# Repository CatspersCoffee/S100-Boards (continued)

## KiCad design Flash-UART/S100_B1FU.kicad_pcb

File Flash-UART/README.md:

# RS232 | TMA | Serial Flash Board Rev 1.0

An S-100 board with a USB serial port (16550 + FT232R), four TMA* bus-master request lines, and four SPI flash chips. The flash chips can be loaded from a PC over USB and then read from the S-100 side (2014–2015).

The idea is fast development turnaround:
1. Program the SPI flash chips from a PC through the CH341A.
2. Flip the RUN/FLASH switch.
3. An S-100 monitor/loader reads the flash contents into RAM through the CPLD's I/O ports.

The S-100 monitor/loader and the PIC18F1330 firmware are **not** in this repo.

## Status
Built. The gerbers are dated 16 Apr 2014 (`GERBERS/`). The CPLD design was brought up in June 2014 and revised in July and December 2015.

## Hardware
| Ref | Part | Role |
|---|---|---|
| U20 | XC95288XL-TQ144 | CPLD: S-100 glue, port decode, SPI bit-bang registers, flash chip select |
| Ux18 | 16550 | UART (clock from oscillator socket Px12 "CLK UART") |
| Ux21 | FT232R | USB to serial for the UART (Jx1) |
| U18 | CH341A | USB to SPI flash programmer (Jx2, 12 MHz crystal X1) |
| U14–U17 | M25P80 | SPI flash chips on a shared bus (U14 on top, U15–U17 on the bottom) |
| U12 | 74LV244 | Switches the flash bus between the CPLD and the CH341A |
| U8 | PIC18F1330 | Reads the RUN/FLASH and F_SEL switches and drives the U12 enables |
| Ux17 | 74LS682N | UART I/O address compare against DIP switch SWx2 |
| U3din1, U3dout1 | 74LS541 | S-100 DO → local data bus, local data bus → S-100 DI |
| U4, U5, U6 | 74LS541 | Address buffers A0–A23 |
| U11 | 74LS541 | TMA0*–TMA3* drivers |
| U19 | 74LS541 | Puts the flash data-out bit on local D0 |
| U7a1, U7b1 | 74HC245 | S-100 status/control input buffers |
| U2, U1, Ux1 | LM1086CS, 7805, 3.3 V SOT-223 | Power |

- **Board:** 10.0 × 5.0 in (254 × 127 mm), plus the S-100 edge-connector tab.
- **KiCad:** pcbnew `(2013-07-07 BZR 4022)-stable`, legacy schematic format (`EESchema Schematic File Version 2`).
- **CPLD tools:** Xilinx ISE 14.7 (`P.20131013`), XC95288XL-10-TQ144.
- **Switches:** RESET (SW1), PIC RESET (SW2), F_SEL (SW4), RUN/FLASH (SW50), DIP switch SWx2 (UART address: A3–A7 on sw 1–5, IORQ on sw 6, sw 7 and 8 to GND).
- **LEDs:** TMA0–TMA3, DONE, B_S (board select), D2, D3, F0–F3 (flash selected), RUN, PROG, TX, RX, and power LEDs for the board, the FT232R and the CH341A.
- **Headers:**
  - XILINX CABLE (JTAG), PIC ISP, FLASH ICP (GND, CLK, Din, CS, Dout on the CH341A side), UART INT
  - CPLD I/O (P10: P110–P112, P2: P113/P115/P116)
  - RDY (P72), RESET (P75)
  - Interrupt Channel Selector (VI0*–VI7*)

## How it works
- **I/O request:** the CPLD makes IOREQ from sINP OR sOUT and passes it to the 74LS682. When A7–A3 and IOREQ match SWx2, the 74LS682 selects the 16550. A2–A0 go straight to the UART. The CPLD makes the UART's RD*/WR* strobes from pDBIN/pWR* and drives the two data-bus buffers.
- **SPI flash ports:** the CPLD decodes ports 90h–97h. A3 is not decoded, so 98h–9Fh mirror them. Each write latches D0, except port 96h, which takes D0–D2.

  | Port | Function |
  |---|---|
  | 90h | CLK |
  | 91h | Din (data to flash) |
  | 92h | CS |
  | 93h | read flash data-out on D0 |
  | 94h | DONE LED |
  | 95h | bit 0: flash select source |
  | 96h | bits 2..0: flash number |

  A loader bit-bangs SPI through these ports.
- **Flash chip select:** the CS from whichever side owns the bus (CPU or CH341A) goes through a 3-to-8 decoder in the CPLD to FLASHSEL0–3 (U14–U17). LEDs F0–F3 show which chip is selected.
  - After reset (port 95h bit 0 = 0) the selection is U16. A note in the CPLD schematic says this position was used for a 256 KB 25L020 "for quick programming".
  - With bit 0 = 1, port 96h picks the chip.
  - In the 2014 CPLD versions the PIC chose the chip instead, through lines PIC18F_0..2.
- **CH341A or S-100:** all four flash chips share CLK/Din/Dout. One half of the 74LV244 connects them to the CPLD, the other half to the CH341A and the FLASH ICP header. The PIC18F1330 enables one half or the other, following the RUN/FLASH switch. At power-up the CPLD (S-100) side has the bus.
- **TMA:** an OUT to port **EEh** latches D0–D3 onto TMA0*–TMA3* (S-100 pins 55, 56, 57, 14) through U11. In U20v2 a 1 asserts the line (low), and reset leaves all four lines high.
- **Reset:** S-100 SLAVE_CLR*, the RESET button or a PIC line clears the CPLD registers and resets the UART. The RESET button also pulls S-100 RESET* (pin 75) through Q8 and jumper JP4.
- **UART:** the 16550's TTL serial lines (SIN, SOUT, RTS, CTS, DTR, DSR) go to the FT232R and USB socket Jx1. The UART interrupt goes to the "UART INT" jumper.

## Files
| Path | What |
|---|---|
| `S100_B1FU.sch`, `S100_B1FU-cache.lib`, `S100_B1FU.pro` | KiCad schematic, symbol cache, project |
| `S100_B1FU.kicad_pcb` | KiCad PCB |
| `S100_B1FU.net`, `S100_B1FU.cmp` | Netlist and component/footprint list |
| `GERBERS/` | Fabrication gerbers and drill file (16 Apr 2014) |
| `cpld/U20v2.sch` | Current CPLD schematic (Xilinx ISE schematic, XML) |
| `cpld/U20v1.sch` | Previous CPLD schematic (July 2015) |
| `cpld/pinmap.ucf` | CPLD pin constraints |
| `cpld/S100BFURev1/S100BFURev1.xise` | ISE project (top: `../U20v2.sch`, constraints `../pinmap.ucf`) |
| `cpld/S100BFURev1/U20v1.jed`, `U20v2.jed` | Programming files |
| `cpld/outdated/` | The first U20 test schematic and pin map (May 2014) |

## History
The git history replays the original dated backups of the KiCad project and the CPLD project, from April 2014 to December 2015.

## Things to check (TODO)
- On the PCB, 16550 (Ux18) pins 18 (WR*), 21 (RD*) and 35 (MR) have no net. The CPLD's RD, WR and RESET outputs (pins 113, 116, 115) only go to header P2. Check the wiring from P2 to the UART.
- CPLD pin 39 (`IOREQtoUx17`, an output) and U7a1 pin 6 (74HC245 output from S-100 pin 69) are on the same net (`/IOREQbb`). Check that only one of them drives it.

## Credits
- The UART section (16550 and FT232R with TTL serial labels, and its schematic notes) follows the N8VEM ECB SBC V2 schematic. Credit to Andrew Lynch and the N8VEM project.
- KiCad symbol libraries include N8VEM community libraries.

## License
Hardware: CERN-OHL-S-2.0 for the original work in this folder; see the repo NOTICE for third-party parts. The bottom-copper text "© 2014 Antony Burrows ALL RIGHTS RESERVED" is left as fabricated; this license applies.

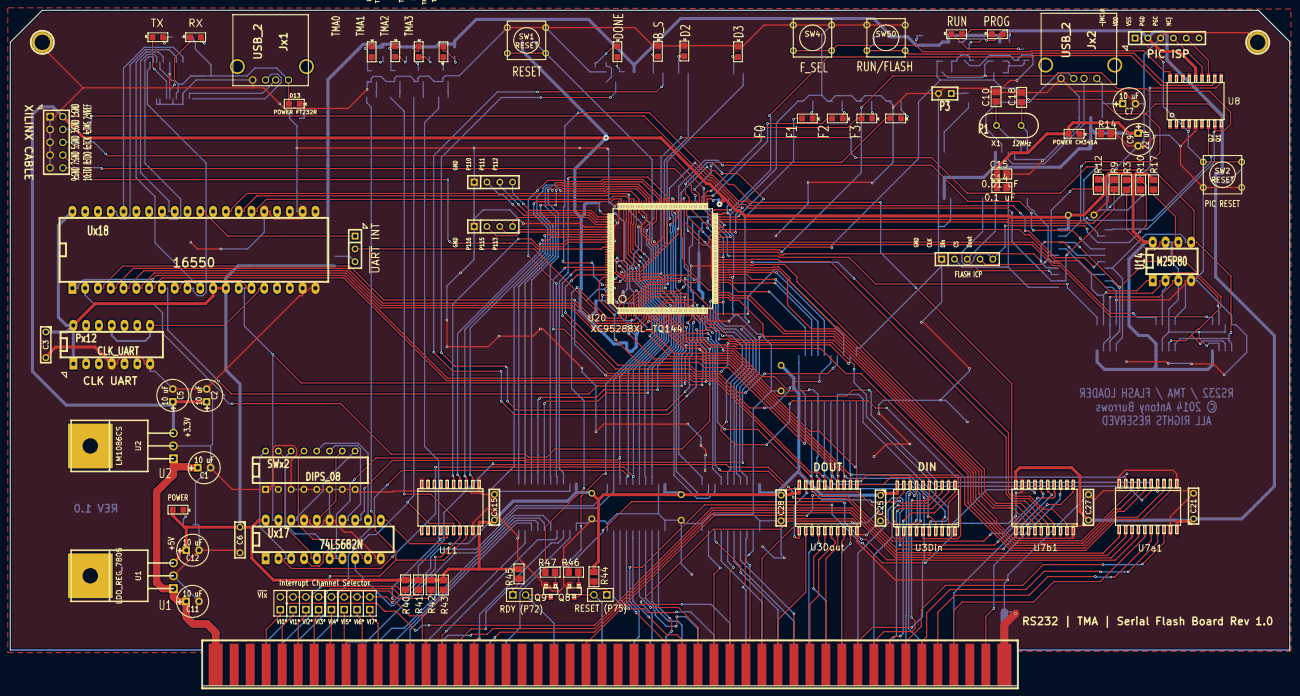
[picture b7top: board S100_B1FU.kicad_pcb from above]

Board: 2 copper layers, 254.0 x 134.1 mm, 164 parts (0 on the bottom side), 254 nets.

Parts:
C1, C2, C5, C7, C11, C12: 10 uF; C1V7
C3, C4, C6, C8, C17, C20, C21, C25, C27, C28: 0.1 uF; C2
C9: 22 uF; C1V7
C10, C18: 15 pF; ^^SMD_Resistor-0805
C14: 0.1 uF; ^^SMD_Resistor-0805
C15: 0.01 uF; ^^SMD_Resistor-0805
C19, C26, C33, C34, C35, C36, C37, C38, C39, C40: C; ^^SMD_Resistor-0805
Cx15: 0.1 uF; C2
D1, D4: LED; ^^LED-0805
D2: P55; ^^LED-0805
D3: P54; ^^LED-0805
D5: POWER; ^^LED-0805
D6: DONE; ^^LED-0805
D7: BOARD_SELECT; ^^LED-0805
D8: POWER CH341A; ^^LED-0805
D9: FLASH_0; ^^LED-0805
D10: FLASH_1; ^^LED-0805
D11: FLASH_2; ^^LED-0805
D12: FLASH_3; ^^LED-0805
D13: POWER FT232R; ^^LED-0805
D14: TMA0; ^^LED-0805
D15: TMA1; ^^LED-0805
D16: TMA2; ^^LED-0805
D17: TMA3; ^^LED-0805
Dx2, Dx3: LED; ^^LED-0805
JP4, JP5: JUMPER; PIN_ARRAY_2X1
JPx1, JPx2, JPx3, JPx4, JPx5, JPx6, JPx7, JPx8: JUMPER; PIN_ARRAY_2X1
Jx1, Jx2: USB_2; USB_A
Kx1: CONN_3; SIL-3
P1: M25P80 ISP; SIL-5
P2, P10: CONN_4; SIL-4
P3: CONN_2; SIL-2
P4: S100_MALE
P5: PIC_ISP; SIL-6
P6, P7: CONN_1; 1pin
P8, P9: CONN_2; ^^SMD_Resistor-0805
P19: XILINX CABLE2; PIN_ARRAY_5x2
Px12: CLK_UART; DIP-14__300_ELL
Q1, Q2, Q3, Q4, Q5, Q6, Q7, Q8, Q9: ^^NPN-SOT23; ^^-SOT23
R1, R5, R6, R13, R14, R15, R16, R20, R21, R22, R23, R24, R29, R31, R33, R35, R37, R39, R40, R41, R42, R43, R44, R45: 330; ^^SMD_Resistor-0805
R2, R7, R18, R19, R28, R32, R34, R36, R38, R46, R47: 470; ^^SMD_Resistor-0805
R3: 1K; ^^SMD_Resistor-0805
R4, R8, R10, R11, R30: 10k; ^^SMD_Resistor-0805
R9, R12, R17: 10K; ^^SMD_Resistor-0805
R25, R26, R27: 100; ^^SMD_Resistor-0805
Rx2: 4700; ^^SMD_Resistor-0805
Rx7, Rx8: 330; ^^SMD_Resistor-0805
SW1, SW2: RESET; SW_PUSH_SMALL
SW4: FLASH_SELECT; SW_PUSH_SMALL
SW50: FLASH/RUN; SW_PUSH_SMALL
SWx2: DIPS_08; 16dip300
U1: LDO_REG_7805; ^^TO220
U2: LM1086CS; ^^TO220
U3din1, U3dout1, U4, U5, U6, U11, U19: ^^74LS541; ^^-SO20W
U7a1, U7b1: 74HC245; ^^-SO20W
U8: PIC18F1330; -SO18-1
U12: ^^74LV244; ^^-SO20W
U14: M25P80; 8DIP-ELL300
U15, U16, U17: M25P80; -SO8
U18: CH341A; -SO28W
U20: XC95288XL-TQ144; -TQFP144
Ux1: ^^3.3VREG_SOT223; -SOT223
Ux17: 74LS682N; 20DIP-ELL300
Ux18: 16550; DIP-40__600_ELL
Ux21: FT232R; -SSOP28
X1: 12MHz; Crystal_HC-49U_Vert

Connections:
/+8V: C1.1, C11.1, P4.1, P4.51, U1.1, U2.1
//CS_UART: U20.25, Ux17.19, Ux18.14
//M1: U7a1.2, U20.20
//WAITtoS100: R47.1, U20.2
/A0: U4.18, U20.100, Ux18.28
/A0b: P4.79, U4.2
/A1: U4.17, U20.101, Ux18.27
/A1b: P4.80, U4.3
/A2: U4.16, U20.102, Ux18.26
/A2b: P4.81, U4.4
/A3: U4.15, U20.103, Ux17.2
/A3b: P4.31, U4.5
/A4: U4.14, U20.104, Ux17.4
/A4b: P4.30, U4.6
/A5: U4.13, U20.105, Ux17.6
/A5b: P4.29, U4.7
/A6: U4.12, U20.106, Ux17.8
/A6b: P4.82, U4.8
/A7: U4.11, U20.107, Ux17.11
/A7b: P4.83, U4.9
/A8: U5.18, U20.79
/A8b: P4.84, U5.2
/A9: U5.17, U20.80
/A9b: P4.34, U5.3
/A10: U5.16, U20.81
/A10b: P4.37, U5.4
/A11: U5.15, U20.82
/A11b: P4.87, U5.5
/A12: U5.14, U20.83
/A12b: P4.33, U5.6
/A13: U5.13, U20.85
/A13b: P4.85, U5.7
/A14: U5.12, U20.86
/A14b: P4.86, U5.8
/A15: U5.11, U20.87
/A15b: P4.32, U5.9
/A16: U6.18, U20.88
/A16b: P4.16, U6.2
/A17: U6.17, U20.91
/A17b: P4.17, U6.3
/A18: U6.16, U20.92
/A18b: P4.15, U6.4
/A19: U6.15, U20.93
/A19b: P4.59, U6.5
/A20: U6.14, U20.94
/A20b: P4.61, U6.6
/A21: U6.13, U20.95
/A21b: P4.62, U6.7
/A22: U6.12, U20.96
/A22b: P4.63, U6.8
/A23: U6.11, U20.97
/A23b: P4.64, U6.9
/BOARD_INTERRUPT_VECT: U7b1.9, U20.5
/BOARD_INTERRUPT_VECTc: JPx1.2, JPx2.2, JPx3.2, JPx4.2, JPx5.2, JPx6.2, JPx7.2, JPx8.2, U7b1.11
/BOARD_SEL_LED: R20.2, U20.31
/CLK_UART: Px12.8, Px12.11, Ux18.16
/CLOCK*: P4.49, U7b1.13
/CLOCK*b: U7b1.7, U20.53
/CPLD2_TCK: R25.1, U20.67
/CPLD2_TDI: R26.1, U20.63
/CPLD2_TDO: P19.8, U20.122
/CPLD2_TMS: R27.1, U20.65
/CPLD_45: U19.2, U20.45
/CPLD_46: U19.3, U20.46
/CPLD_48: U19.4, U20.48
/CPLD_49: U19.5, U20.49
/CPLD_130: U19.6, U20.130
/CPLD_131: U19.7, U20.131
/CPLD_132: U19.8, U20.132
/CPLD_133: U19.9, U20.133
/CPLD_134: U19.1, U19.19, U20.134
/CPLD_M25P80_CLK: U12.2, U20.135
/CPLD_M25P80_CS: U12.6, U20.137
/CPLD_M25P80_Din: U12.4, U20.136
/CPLD_M25P80_Dout: R9.2, U12.12, U20.138
/CTS_TTL: Ux18.36, Ux21.11
/D0: U3din1.18, U3dout1.2, U19.18, U20.9, U20.17, Ux18.1
/D1: U3din1.17, U3dout1.3, U19.17, U20.10, U20.19, Ux18.2
/D2: U3din1.16, U3dout1.4, U19.16, U20.11, Ux18.3
/D3: U3din1.15, U3dout1.5, U19.15, U20.12, Ux18.4
/D4: U3din1.14, U3dout1.6, U19.14, U20.13, Ux18.5
/D5: U3din1.13, U3dout1.7, U19.13, U20.14, Ux18.6
/D6: U3din1.12, U3dout1.8, U19.12, U20.15, Ux18.7
/D7: U3din1.11, U3dout1.9, U19.11, U20.16, Ux18.8
/DBUSIN_EN: U3din1.1, U3din1.19, U20.22
/DBUSOUT_EN: U3dout1.1, U3dout1.19, U20.21
/DI0b: P4.95, U3dout1.18
/DI1b: P4.94, U3dout1.17
/DI2b: P4.41, U3dout1.16
/DI3b: P4.42, U3dout1.15
/DI4b: P4.91, U3dout1.14
/DI5b: P4.92, U3dout1.13
/DI6b: P4.93, U3dout1.12
/DI7b: P4.43, U3dout1.11
/DO0b: P4.36, U3din1.2
/DO1b: P4.35, U3din1.3
/DO2b: P4.88, U3din1.4
/DO3b: P4.89, U3din1.5
/DO4b: P4.38, U3din1.6
/DO5b: P4.39, U3din1.7
/DO6b: P4.40, U3din1.8
/DO7b: P4.90, U3din1.9
/DONE_LED: R7.2, U20.30
/DSR_TTL: Ux18.37, Ux21.9
/DTR_TTL: Ux18.33, Ux21.2
/FLASH_0: D9.1, U20.71
/FLASH_1: D10.1, U20.74
/FLASH_2: D11.1, U20.75
/FLASH_3: D12.1, U20.76
/FLASH_CS: U12.5, U12.14, U20.57
/FLASH_SEL_0: U14.1, U20.66
/FLASH_SEL_1: U15.1, U20.64
/FLASH_SEL_2: U16.1, U20.61
/FLASH_SEL_3: U17.1, U20.60
/IOREQb: P4.69, U7a1.14
/IOREQbb: U7a1.6, U20.39, Ux17.13
/LED_D2: R13.2, U20.7
/LED_D3: R16.2, U20.6
/M2_MCLR: P5.1, R4.2, SW2.1, U8.4
/M2_PGC: P5.5, U8.12
/M2_PGD: P5.4, U8.13
/MWRT: P4.68, U7a1.13
/MWRTb: U7a1.7, U20.40
/NDEF2: P4.65, U7a1.12
/NDEF2b: U7a1.8, U20.41
/PHI: P4.24, U7b1.14
/PHIb: U7b1.6, U20.54
/PIC18F_0: U8.11, U20.68
/PIC18F_1: U8.10, U20.69
/PIC18F_2: U8.7, U20.70
/PROG_M25P80_CLK: P1.2, U12.11, U18.18
/PROG_M25P80_CS: P1.4, U12.15, U18.15
/PROG_M25P80_Din: P1.3, U12.13, U18.20
/PROG_M25P80_Dout: P1.5, R10.2, U12.3, U18.22
/Q1: R2.2, R18.2, U8.9, U12.19, U20.59
/Q2: R19.2, R28.2, U8.8, U12.1, U20.58
/RDY: JP5.2, P4.72, Q9.3
/RESET*: JP4.2, P4.75, Q8.3
/RESETtoS100: R46.1, U20.3
/RTS_TTL: Ux18.32, Ux21.3
/SIN_TTL: Ux18.10, Ux21.1
/SLAVE_CLR*: P4.54, U7a1.11
/SLAVE_CLR*vv: U7a1.9, U20.33
/SOUT_TTL: Ux18.11, Ux21.5
/TMA0*: P4.55, R32.1, R40.1, U11.18
/TMA0_CPLD: U11.2, U20.117
/TMA1*: P4.56, R34.1, R41.1, U11.17
/TMA1_CPLD: U11.3, U20.118
/TMA2*: P4.57, R36.1, R42.1, U11.16
/TMA2_CPLD: U11.4, U20.119
/TMA3*: P4.14, R38.1, R43.1, U11.15
/TMA3_CPLD: U11.5, U20.120
/UART_INT: Kx1.1, Ux18.30
/USB_VCC0: D13.1, Jx1.1, Rx7.1, Rx8.1, Ux21.4, Ux21.20
/USB_VCC1: C7.1, Jx2.1, Ux1.3
/V3.3: C2.1, C4.1, C5.1, C19.1, C26.1, C33.1, C34.1, C35.1, C36.1, C37.1, C38.1, C39.1, C40.1, P8.1, P8.2, P9.1, P9.2, P19.2, R3.2, R8.1, R12.1, R17.1, U2.3, U12.20, U14.8, U15.8, U16.8, U17.8, U20.1, U20.8, U20.37, U20.42, U20.55, U20.73, U20.84, U20.109, U20.127, U20.141
/V3.3b: C9.1, C14.1, C15.1, D8.1, U18.9, U18.28, Ux1.2, Ux1.4
/VI0*: JPx1.1, P4.4
/VI1*: JPx2.1, P4.5
/VI2*: JPx3.1, P4.6
/VI3*: JPx4.1, P4.7
/VI4*: JPx5.1, P4.8
/VI5*: JPx6.1, P4.9
/VI6*: JPx7.1, P4.10
/VI7*: JPx8.1, P4.11
/pDBIN: P4.78, U7b1.16
/pDBINb: U7b1.4, U20.51
/pWR*: P4.77, U7b1.17
/pWR*b: U7b1.3, U20.50
/sINP: P4.46, U7a1.16
/sINPb: U7a1.4, U20.35
/sM1: P4.44, U7a1.18
/sMEMR: P4.47, U7a1.15
/sMEMRb: U7a1.5, U20.38
/sOUT: P4.45, U7a1.17
/sOUTb: U7a1.3, U20.34
/sWO*: P4.97, U7b1.15
/sWO*b: U7b1.5, U20.52
/~UART_INT: Kx1.2, U20.4
GND: C1.2, C2.2, C3.2, C4.2, C5.2, C6.2, C7.2, C8.2, C9.2, C10.2, C11.2, C12.2, C14.2, C15.2, C17.2, C18.2, C19.2, C20.2, C21.2, C25.2, C26.2, C27.2, C28.2, C33.2, C34.2, C35.2, C36.2, C37.2, C38.2, C39.2, C40.2, Cx15.2, D2.2, D3.2, D7.2, Jx1.4, Jx2.4, P1.1, P2.1, P3.2, P4.50, P4.100, P5.3, P6.1, P7.1, P10.1, P19.1, P19.3, P19.5, P19.7, P19.9, Px12.4, Px12.7, Q1.2, Q2.2, Q3.2, Q4.2, Q5.2, Q6.2, Q7.2, Q8.2, Q9.2, R5.2, R9.1, R10.1, R14.2, R21.1, R22.1, R23.1, R24.1, R31.2, SW1.1, SW2.2, SW4.1, SW50.1, SWx2.1, SWx2.2, SWx2.3, SWx2.4, SWx2.5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
unnamed: R15.2, U18.1
unnamed: P10.4, U20.110
unnamed: P10.3, U20.111
unnamed: P10.2, U20.112
unnamed: P2.4, U20.113
unnamed: P2.3, U20.115
unnamed: P2.2, U20.116
unnamed: D17.1, R39.1
unnamed: Q7.1, R38.2
unnamed: D16.2, Q6.3
unnamed: D16.1, R37.1
unnamed: Q6.1, R36.2
unnamed: D17.2, Q7.3
unnamed: JP5.1, R45.1
unnamed: Q9.1, R47.2
unnamed: JP4.1, R44.1
unnamed: Q8.1, R46.2
unnamed: D14.1, R33.1
unnamed: D14.2, Q4.3
unnamed: Q4.1, R32.2
unnamed: D15.1, R35.1
unnamed: D15.2, Q5.3
unnamed: Q5.1, R34.2
unnamed: R8.2, SW1.2, U20.24
unnamed: P3.1, R15.1
unnamed: D8.2, R14.1
unnamed: Jx2.2, U18.11
unnamed: Jx2.3, U18.10
unnamed: C10.1, U18.13, X1.1
unnamed: C18.1, U18.14, X1.2
unnamed: D9.2, R21.2
unnamed: D10.2, R22.2
unnamed: D11.2, R23.2
unnamed: D12.2, R24.2
unnamed: R11.2, SW4.2, U8.18
unnamed: D4.2, Q2.3
unnamed: D13.2, R31.1
unnamed: Ux18.9, Ux18.15
unnamed: Dx2.2, Ux21.23
unnamed: Dx3.2, Ux21.22
unnamed: Dx2.1, Rx7.2
unnamed: Dx3.1, Rx8.2
unnamed: Jx1.2, Ux21.16
unnamed: Jx1.3, Ux21.15
unnamed: Kx1.3, Rx2.2
unnamed: P19.10, R26.2
unnamed: P19.6, R25.2
unnamed: P19.4, R27.2
unnamed: R30.2, SW50.2, U8.17
unnamed: D4.1, R29.1
unnamed: SWx2.16, Ux17.3
unnamed: SWx2.15, Ux17.5
unnamed: SWx2.14, Ux17.7
unnamed: SWx2.13, Ux17.9
unnamed: SWx2.11, Ux17.14
unnamed: SWx2.12, Ux17.12
unnamed: SWx2.10, Ux17.16
unnamed: SWx2.9, Ux17.18
unnamed: D1.1, R1.1
unnamed: D1.2, Q1.3
unnamed: R3.1, U14.3, U14.7, U15.3, U15.7, U16.3, U16.7, U17.3, U17.7
unnamed: R12.2, U12.7, U12.16, U14.5, U15.5, U16.5, U17.5
unnamed: R17.2, U12.9, U12.18, U14.6, U15.6, U16.6, U17.6
unnamed: U12.8, U12.17, U14.2, U15.2, U16.2, U17.2
unnamed: D6.1, R6.1
unnamed: D6.2, Q3.3
unnamed: Q3.1, R7.1
unnamed: D5.2, R5.1
unnamed: D7.1, R20.1
unnamed: D2.1, R13.1
unnamed: Q2.1, R18.1, R28.1
unnamed: Q1.1, R2.1, R19.1
unnamed: D3.1, R16.1
VCC: C3.1, C6.1, C8.1, C12.1, C17.1, C20.1, C21.1, C25.1, C27.1, C28.1, Cx15.1, D5.1, P5.2, Px12.1, Px12.14, R1.2, R4.1, R6.2, R11.1, R29.2, R30.1, R33.2, R35.2, R37.2, R39.2, R40.2, R41.2, R42.2, R43.2, R44.2, R45.2, Rx2.1, U1.3, U3din1.20, U3dout1.20, U4.20, U5.20, U6.20, U7a1.20, U7b1.20, U8.14, U11.20, U19.20, Ux17.20, Ux18.12, Ux18.13, Ux18.40

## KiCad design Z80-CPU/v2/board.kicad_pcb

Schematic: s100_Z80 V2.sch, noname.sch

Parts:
C1: 47 uF; C1V7
C2, C4: 0.1 uF
C3: 0.1 uF; C1V7
C7, C8, C9, C10, C11, C12, C13, C14, C15, C16, C18, C19, C20, C23, C24, C25, C26, C27, C28, C29, C30, C36, C37, C38, C39, C40, C41, C45, C46, C47, C48, C49, C50, C51, C52, C53, C54, C58, C59, C60, C62, C63: 0.1 uF; C2
C42: 22 uF; C1V7
C43: 33 uF; C1V7
D1, D2, D3, D4, D5, D7: DONE
D6: 1N4148; D3
JP4, JP5, JP6, JP7: JUMPER; SIL-2
K1, K2, K4: CONN_3; SIL-3
P1: S100_MALE
P2: CONN_4X2; pin_array_4x2
P3, P5: CLK_CPU
P4, P37: CONN_2X2; PIN_ARRAY_2X2
P6: CLK_SEL
P34, P35: CONN_1; 1pin
P36: CONN_3X2; pin_array_3x2
Px1, Px2, Px3, Px4, Px5: CONN_8
Q1: 2N3904; TO92-INVERT
Q2, Q3, Q4, Q5, Q6, Q7: ^^NPN-SOT23
R1, R3, R7, R9, R12, R14: 330
R2, R6, R8, R10, R13, R15: 470
R4: 4K7; R3
R5: 330; R3
R11, R39, R41: 4700; R3
R35, R36, R37, R38: 10; R3
RR2, RR3, RR4, RR5, RR6, RR8, RR9: 1000; r_pack9
RR7: 4700; r_pack9
SW2, SW3, SW4: DIPS_08; SWDIP8
U, U43: 74LS11; 14dip300
U1: Z80; 40dip600
U2, U3, U12, U22: 74LS373; 20dip300
U4, U6: 74LS153; 16dip300
U5, U8: 74LS157; 16dip300
U7, U44: 74LS32
U9, U10, U11: 74LS165; 16dip300
U13: 2732
U14: 74LS682N; 20dip300
U16, U17: 74LS273; 20dip300
U19, U20, U21: 74LS244; 20dip300
U23, U45: 74LS02; 14dip300
U24, U25, U36, U47: 74LS04; 14dip300
U26, U37: 74LS05; 14dip300
U27: 74LS139; 16dip300
U28, U31, U49: 74LS00; 14dip300
U29, U30, U32, U33, U34: 74LS74; 14dip300
U35: 74LS32; 14dip300
U38: 74F04; 14dip300
U39: 74S08; 14dip300
U40: 74S00; 14dip300
U41: 74LS27; 14dip300
U42: 2.0000 MHz; 14dip300
U48: LDO_REG_7805

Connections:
/27_ROM_OE: U13.20 (~G), U28.10, U47.3, U49.3
/+8V: C1.1, P1.1 (+8_V), P1.51 (+8_V), U48.1 (VI)
/A0: P1.79 (A0), U2.2 (O0)
/A1: P1.80 (A1), U2.5 (O1)
/A2: P1.81 (A2), U2.6 (O2)
/A3: P1.31 (A3), U2.9 (O3)
/A4: P1.30 (A4), U2.12 (O4)
/A5: P1.29 (A5), U2.15 (O5)
/A6: P1.82 (A6), U2.16 (O6)
/A7: P1.83 (A7), U2.19 (O7)
/A8: P1.84 (A8), U3.19 (O7)
/A9: P1.34 (A9), U3.16 (O6)
/A10: P1.37 (A10), U3.15 (O5)
/A11: P1.87 (A11), U3.12 (O4)
/A12: P1.33 (A12), U3.9 (O3)
/A13: P1.85 (A13), U3.6 (O2)
/A14: P1.86 (A14), U3.5 (O1)
/A15: P1.32 (A15), U3.2 (O0)
/A16: P1.16 (A16), U12.19 (O7)
/A17: P1.17 (A17), U12.16 (O6)
/A18: P1.15 (A18), U12.15 (O5)
/A19: P1.59 (A19), U12.12 (O4)
/A20: P1.61 (A20), U12.9 (O3)
/A21: P1.62 (A21), U12.6 (O2)
/A22: P1.63 (A22), U12.5 (O1)
/A23: P1.64 (A23), U12.2 (O0)
/ADSB: U2.1 (OE), U3.1 (OE), U12.1 (OE), U24.2
/ADSB*: P1.22 (ADSB*), RR5.9, U24.1, U37.4
/BUSAK*: Px2.7, U1.23 (BUSAK), U26.9, U37.11
/BUSRQ*: Px2.6, U1.25 (BUSRQ), U34.5 (Q)
/BUS_IN: U31.3, U32.12 (D), U32.13 (Cd)
/CDSB*: P1.19 (CDSB*), RR8.2, U37.8, U37.13
/CLK: Px2.8, R5.2, U1.6 (CLK), U36.2
/CLK_CPU: P6.2, P6.4, P6.6, U36.3
/CLOCK*: P1.49 (CLOCK), P4.2
/D0: Px3.1, U1.14 (D0), U13.9 (Q0), U16.18 (D7), U17.18 (D7), U19.17 (I3b), U20.3 (O3b)
/D1: Px3.2, U1.15 (D1), U13.10 (Q1), U16.17 (D6), U17.17 (D6), U19.15 (I2b), U20.5 (O2b)
/D2: Px3.3, U1.12 (D2), U13.11 (Q2), U16.14 (D5), U17.14 (D5), U19.13 (I1b), U20.7 (O1b)
/D3: Px3.4, U1.8 (D3), U13.13 (Q3), U16.13 (D4), U17.13 (D4), U19.11 (I0b), U20.9 (O0b)
/D4: Px3.5, U1.7 (D4), U13.14 (Q4), U16.8 (D3), U17.8 (D3), U19.8 (I3a), U20.12 (O3a)
/D5: Px3.6, U1.9 (D5), U13.15 (Q5), U16.7 (D2), U17.7 (D2), U19.6 (I2a), U20.14 (O2a)
/D6: Px3.7, U1.10 (D6), U13.16 (Q6), U16.4 (D1), U17.4 (D1), U19.4 (I1a), U20.16 (O1a)
/D7: Px3.8, U1.13 (D7), U13.17 (Q7), U16.3 (D0), U17.3 (D0), U19.2 (I0a), U20.18 (O0a)
/DATA_OUT_ENABLE: U20.1 (OEa), U20.19 (OEb), U28.1, U28.8
/DI0: P1.95 (DI1_OD1), U20.17 (I3b)
/DI1: P1.94 (DI1_OD1), U20.15 (I2b)
/DI2: P1.41 (D12_OD2), U20.13 (I1b)
/DI3: P1.42 (D13_OD3), U20.11 (I0b)
/DI4: P1.91 (DI4_OD4), U20.8 (I3a)
/DI5: P1.92 (DI5_OD5), U20.6 (I2a)
/DI6: P1.93 (DI6_OD6), U20.4 (I1a)
/DI7: P1.43 (D17_OD7), U20.2 (I0a)
/DO0: P1.36 (DO0_ED0), U19.3 (O3b)
/DO1: P1.35 (DO1_ED1), U19.5 (O2b)
/DO2: P1.88 (DO2_ED2), U19.7 (O1b)
/DO3: P1.89 (DO3_ED3), U19.9 (O0b)
/DO4: P1.38 (DO4_ED4), U19.12 (O3a)
/DO5: P1.39 (DO5_ED5), U19.14 (O2a)
/DO6: P1.40 (DO6_ED6), U19.16 (O1a)
/DO7: P1.90 (DO7_ED7), U19.18 (O0a)
/DODSB*: P1.23 (DODSB*), RR5.8, U28.2, U37.2
/END_SYNC: U30.8 (~Q), U35.13, U40.1
/ERROR*: P1.98 (ERROR*), RR8.10
/HALT*: Px1.8, U1.18 (HALT), U38.1
/HOLD*: P1.74 (HOLD*), RR5.4, U34.2 (D), U45.2
/INT*: P1.73 (INT*), RR5.3, U21.17 (I3b)
/IORQ: U8.1 (S), U23.2, U23.12, U30.1 (Cd), U30.2 (D), U31.10, U38.6, U39.2, U39.12, U40.5
/IORQ*: Px1.4, U1.20 (IORQ), U38.5
/M1*: Px1.2, U1.27 (M1), U38.13
/M1_WAIT: P36.3, U38.10, U39.4, U39.10
/MEM_RD: U22.8 (D3), U39.8, U49.2
/MEM_WAIT: P36.5, U22.14 (D5), U38.12, U40.4
/MREQ*: Px1.3, U1.19 (MREQ), U38.11
/MWRT: P1.68 (MWRT), P4.4
/NDEF3: P1.66 (NDEF3), P6.5
/NMI*: K1.2 (PM), K1.3, P1.12 (NMI*), Px2.4, RR6.5, U1.17 (NMI)
/PARTIAL_LATCH: P37.2, U2.11 (LE), U3.11 (LE), U12.11 (LE), U32.5 (Q)
/PHANTOM*: P1.67 (PHANTOM*), RR8.9
/PHI: P1.24 (PHI), R41.2, U21.9 (O0b)
/POC*: JP4.1, P1.99 (POC*), RR6.7
/PU1K-BB: P1.4 (VIO*), RR9.2
/PU1K-CC: P1.5 (VI1*), RR9.3
/PU1K-D: P1.72 (RDY), RR5.5, U43.2
/PU1K-DD: P1.6 (VI2*), RR9.4
/PU1K-E: P1.3 (XRDY), RR5.6, U43.13
/PU1K-EE: P1.7 (VI3*), RR9.5
/PU1K-F: RR5.7, U21.1 (OEa), U37.12
/PU1K-FF: P1.8 (VI4*), RR9.6
/PU1K-GG: P1.9 (VI5*), RR9.7
/PU1K-HH: P1.10 (VI6*), RR9.8
/PU1K-I: JP6.1, P1.54 (SLAVE_CLR*), RR5.10
/PU1K-II: P1.11 (VI7*), RR9.9
/PU1K-J: RR6.2, U26.8, U33.12 (D), U33.13 (Cd)
/PU1K-JJ: P1.60 (SIXTN*), RR9.10
/PU1K-K: P1.26 (pHDLA), RR6.3, U37.10
/PU1K-L: RR6.4, U26.10, U30.10 (Sd)
/PU1K-N: K2.1, RR6.6
/PU1K-P: JP5.1, JP7.2, P1.75 (RESET*), Px2.5, RR6.8, U1.26 (RESET), U34.10 (Sd), U35.1, U35.2
/PU1K-Q: C43.1, D6.1 (A), JP5.2, RR6.9
/PU1K-R: RR6.10, U30.4 (Sd), U30.13 (Cd)
/PU1K-T: P1.18 (SDSB*), RR8.3, U25.3, U37.6
/PU1K-U: P1.14 (TMA3*), RR8.4
/PU1K-V: P1.57 (TMA2*), RR8.5
/PU1K-W: P1.56 (TMA1*), RR8.6
/PU1K-X: P1.55 (TMA0*), RR8.7
/PU1K-Y: P1.58 (sXTRQ*), RR8.8
/PU5K-A: RR7.2, U33.10 (Sd)
/PU5K-B: RR7.3, U34.1 (Cd), U34.4 (Sd)
/PU5K-C: RR7.4, U32.1 (Cd), U32.4 (Sd)
/PU5K-D: RR7.5, U33.1 (Cd), U33.4 (Sd)
/PU5K-F: RR7.7, U32.10 (Sd)
/PU5K-G: Q1.3 (C), RR7.8, RR7.10, U26.3, U26.5, U26.13
/PWRFAIL*: K1.1, P1.13 (PWRFAIL*)
/RD*: Px1.6, U1.21 (RD), U31.1, U38.9, U40.10
/READ_STROBE: U21.2 (I0a), U28.9, U32.9 (Q)
/REFSH*: Px1.7, U1.28 (REFSH), U25.13, U39.5
/ROM_SELECT: R6.2, U31.13, U47.4
/START_SYNC: U26.11, U30.12 (D), U32.2 (D), U35.12, U41.12
/WAIT*: Px2.2, U1.24 (WAIT), U43.12
/WR*: Px1.5, U1.22 (WR), U38.3, U40.13
/Z80_ACTIVE: R2.2, U34.9 (Q)
/bA0: Px4.1, U1.30 (A0), U2.3 (D0), U13.8 (A0), U27.2 (A0)
/bA1: Px4.2, U1.31 (A1), U2.4 (D1), U13.7 (A1), U27.3 (A1)
/bA2: Px4.3, U1.32 (A2), U2.7 (D2), U13.6 (A2), U14.6 (P2)
/bA3: Px4.4, U1.33 (A3), U2.8 (D3), U13.5 (A3), U14.8 (P3)
/bA4: Px4.5, U1.34 (A4), U2.13 (D4), U13.4 (A4), U14.11 (P4)
/bA5: Px4.6, U1.35 (A5), U2.14 (D5), U13.3 (A5), U14.13 (P5)
/bA6: Px4.7, U1.36 (A6), U2.17 (D6), U13.2 (A6), U14.15 (P6)
/bA7: Px4.8, U1.37 (A7), U2.18 (D7), U13.1 (A7), U14.17 (P7)
/bA8: Px5.1, U1.38 (A8), U8.14 (I0c), U13.23 (A8)
/bA9: Px5.2, U1.39 (A9), U8.11 (I0d), U13.22 (A9)
/bA10: Px5.3, U1.40 (A10), U8.5 (I0b), U13.19 (A10)
/bA11: Px5.4, U1.1 (A11), U8.2 (I0a), U13.21 (A11)
/bA12: Px5.5, U1.2 (A12), U4.3 (I3a), U4.4 (I2a), U4.5 (I1a), U7.1
/bA13: Px5.6, U1.3 (A13), U4.11 (I1b), U4.12 (I2b), U4.13 (I3b), U7.2
/bA14: Px5.7, U1.4 (A14), U5.1 (S), U6.3 (I3a), U7.4, U23.5, U25.5
/bA15: Px5.8, U1.5 (A15), U5.15 (E), U6.13 (I3b), U7.5, U23.6, U23.9
/bA16: R8.2, U5.12 (Zc), U12.18 (D7)
/bA17: R10.2, U5.9 (Zd), U12.17 (D6)
/bA18: R13.2, U5.7 (Zb), U12.14 (D5)
/bA19: R15.2, U5.4 (Za), U12.13 (D4)
/bINT*: Px2.3, U1.16 (INT), U21.3 (O3b)
/pDBIN: P1.78 (pDBIN), R35.1
/pSTVAL*: P1.25 (pSTVAL*), R37.1
/pSYNC: P1.76 (pSYNC), R36.1
/pSYNC_RAW: P37.4, U21.4 (I1a), U31.4, U31.9, U31.12, U41.6, U43.11
/pWR*: P1.77 (pWR*), R38.1
/sHLTA: P1.48 (sHLTA), U22.2 (O0)
/sINP: P1.46 (sINP), U22.6 (O2)
/sINTA: P1.96 (sINTA), P36.1, U22.16 (O6)
/sM1: P1.44 (sM1), U22.15 (O5)
/sMEMR: P1.47 (sMEMR), U22.9 (O3)
/sOUT: P1.45 (sOUT), U22.5 (O1), U28.12
/sWO*: P1.97 (sWO*), U22.12 (O4)
GND: C1.2, C2.2, C3.2, C4.2, C7.2, C8.2, C9.2, C10.2, C11.2, C12.2, C13.2, C14.2, C15.2, C16.2, C18.2, C19.2, C20.2, C23.2, C24.2, C25.2, C26.2, C27.2, C28.2, C29.2, C30.2, C36.2, C37.2, C38.2, C39.2, C40.2, C41.2, C42.2, C43.2, C45.2, C46.2, C47.2, C48.2, C49.2, C50.2, C51.2, C52.2, C53.2, C54.2, C58.2, C59.2, C60.2, C62.2, C63.2, K4.1, P1.50 (0_V2), P1.100 (0_V5), P2.2, P2.4, P2.6, P2.8, P3.4, P3.7, P5.4, P5.7, P34.1, P35.1, Px1.1, Px2.1, Q1.1 (E), Q2.2 (E), Q3.2 (E), Q4.2 (E), Q5.2 (E), Q6.2 (E), Q7.2 (E), SW2.1, SW2.2, SW2.3, SW2.4, SW2.5, SW2.6, SW2.7, SW2.8, SW3.1, SW3.2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
unnamed: U33.2 (D), U45.1
unnamed: K2.3, U33.6 (~Q)
unnamed: U33.8 (~Q), U45.3
unnamed: R37.2, U21.14 (O2a)
unnamed: R35.2, U21.18 (O0a)
unnamed: K2.2 (PM), U34.12 (D), U34.13 (Cd)
unnamed: U22.7 (D2), U39.11
unnamed: U38.8, U39.9, U39.13
unnamed: U22.3 (D0), U38.2
unnamed: U22.17 (D6), U41.1, U45.10
unnamed: U30.5 (Q), U41.13
unnamed: RR4.9, SW4.16, U11.11 (P0)
unnamed: RR4.3, SW4.10, U11.5 (P6)
unnamed: RR4.5, SW4.12, U11.3 (P4)
unnamed: RR4.7, SW4.14, U11.13 (P2)
unnamed: RR4.2, SW4.9, U11.6 (P7)
unnamed: U11.1 (Pl), U31.11
unnamed: RR2.9, SW2.16, U9.11 (P0)
unnamed: RR2.7, SW2.14, U9.13 (P2)
unnamed: RR2.5, SW2.12, U9.3 (P4)
unnamed: RR2.3, SW2.10, U9.5 (P6)
unnamed: RR4.8, SW4.15, U11.12 (P1)
unnamed: RR4.6, SW4.13, U11.14 (P3)
unnamed: RR4.4, SW4.11, U11.4 (P5)
unnamed: RR2.8, SW2.15, U9.12 (P1)
unnamed: RR2.2, SW2.9, U9.6 (P7)
unnamed: RR2.4, SW2.11, U9.4 (P5)
unnamed: RR2.6, SW2.13, U9.14 (P3)
unnamed: U3.7 (D2), U4.9 (Zb)
unnamed: U3.18 (D7), U8.12 (Zc)
unnamed: U3.14 (D5), U8.7 (Zb)
unnamed: U3.3 (D0), U6.9 (Zb)
unnamed: U5.11 (I0d), U16.6 (Q2)
unnamed: U6.5 (I1a), U16.15 (Q5)
unnamed: U5.13 (I1c), U17.9 (Q3)
unnamed: U6.4 (I2a), U17.15 (Q5)
unnamed: U5.3 (I1a), U17.2 (Q0)
unnamed: U5.2 (I0a), U16.2 (Q0)
unnamed: U14.19 (P=Q), U25.1
unnamed: U16.11 (Cp), U27.6 (O2)
unnamed: U16.1 (Mr), U17.1 (Mr), U35.3
unnamed: U7.9, U17.19 (Q7)
unnamed: D5.1 (A), R12.1
unnamed: Q6.1 (B), R13.1
unnamed: D5.2 (K), Q6.3 (C)
unnamed: D7.1 (A), R14.1
unnamed: Q7.1 (B), R15.1
unnamed: D7.2 (K), Q7.3 (C)
unnamed: D1.1 (A), R1.1
unnamed: D4.1 (A), R9.1
unnamed: D4.2 (K), Q5.3 (C)
unnamed: Q5.1 (B), R10.1
unnamed: U7.11, U44.2
unnamed: K4.3, R4.2
unnamed: U44.3, U47.1
unnamed: D3.1 (A), R7.1
unnamed: Q4.1 (B), R8.1
unnamed: D3.2 (K), Q4.3 (C)
unnamed: U4.2 (S1), U6.2 (S1), U23.13
unnamed: U21.6 (I2a), U36.12
unnamed: RR3.9, SW3.16, U10.11 (P0)
unnamed: RR3.7, SW3.14, U10.13 (P2)
unnamed: RR3.5, SW3.12, U10.3 (P4)
unnamed: RR3.3, SW3.10, U10.5 (P6)
unnamed: U10.1 (Pl), U31.8
unnamed: RR3.2, SW3.9, U10.6 (P7)
unnamed: RR3.4, SW3.11, U10.4 (P5)
unnamed: RR3.6, SW3.13, U10.14 (P3)
unnamed: RR3.8, SW3.15, U10.12 (P1)
unnamed: U11.7 (~Q7), U35.4
unnamed: Q2.1 (B), R2.1
unnamed: D1.2 (K), Q2.3 (C)
unnamed: D2.1 (A), R3.1
unnamed: D2.2 (K), Q3.3 (C)
unnamed: Q3.1 (B), R6.1
unnamed: U38.4, U39.1, U40.2
unnamed: P36.2, P36.4, P36.6, U31.5
unnamed: U36.11, U36.13, U43.8
unnamed: JP7.1, U26.12
unnamed: U22.4 (D1), U39.3, U45.6
unnamed: U22.1 (OE), U25.4
unnamed: P37.1, P37.3, R39.2, U22.11 (LE)
unnamed: U4.14 (S0), U6.14 (S0), U23.1
unnamed: U32.11 (Cp), U36.8
unnamed: U21.8 (I3a), U40.3, U45.5
unnamed: JP6.2, U26.6
unnamed: U23.8, U25.6
unnamed: U33.5 (Q), U37.9
unnamed: U24.12, U43.1
unnamed: U22.13 (D4), U45.13
unnamed: U9.1 (Pl), U31.6
unnamed: U9.7 (~Q7), U35.10
unnamed: U10.7 (~Q7), U35.5
unnamed: P3.8, P3.11, P6.3
unnamed: U7.3, U7.12
unnamed: U7.8, U44.1
unnamed: U7.6, U7.13
unnamed: K4.2 (PM), U7.10
unnamed: P5.8, P5.11, P6.1
unnamed: U5.10 (I1d), U17.6 (Q2)
unnamed: U5.6 (I1b), U17.5 (Q1)
unnamed: U6.12 (I2b), U17.12 (Q4)
unnamed: U6.11 (I1b), U16.12 (Q4)
unnamed: U39.6, U40.9, U41.2
unnamed: U21.11 (I0b), U30.3 (Cp), U30.11 (Cp), U33.3 (Cp), U34.3 (Cp), U34.11 (Cp), U36.1, U36.4, U36.5
unnamed: U21.15 (I2b), U45.4
unnamed: U21.19 (OEb), U34.8 (~Q)
unnamed: R36.2, U21.16 (O1a)
unnamed: R38.2, U21.12 (O3a)
unnamed: U25.12, U41.5
unnamed: U9.2 (CP), U10.2 (CP), U11.2 (CP), U32.3 (Cp), U33.11 (Cp), U36.6, U43.9
unnamed: U3.8 (D3), U4.7 (Za)
unnamed: U3.13 (D4), U8.4 (Za)
unnamed: U3.17 (D6), U8.9 (Zd)
unnamed: U5.14 (I0c), U16.9 (Q3)
unnamed: U5.5 (I0b), U16.5 (Q1)
unnamed: U3.4 (D1), U6.7 (Za)
unnamed: U17.11 (Cp), U27.7 (O3)
unnamed: U21.13 (I1b), U42.8, U42.9, U42.10, U42.11
unnamed: U33.9 (Q), U37.1, U37.3, U37.5
unnamed: P4.1, U21.7 (O1b)
unnamed: P4.3, U21.5 (O2b)
unnamed: U24.13, U35.8
unnamed: U35.6, U35.9
unnamed: U35.11, U41.4
unnamed: U36.9, U36.10
unnamed: P2.1, U14.12 (Q4)
unnamed: P2.3, U14.14 (Q5)
unnamed: P2.5, U14.16 (Q6)
unnamed: P2.7, U14.18 (Q7)
unnamed: U40.11, U45.11, U45.12
unnamed: U31.2, U40.6, U45.8, U45.9
unnamed: C42.1, Q1.2 (B), R11.2
unnamed: JP4.2, U26.4
unnamed: U47.2, U49.1
unnamed: U19.1 (OEa), U19.19 (OEb), U28.3
unnamed: U40.8, U40.12
unnamed: U23.4, U23.11
unnamed: U23.3, U23.10
unnamed: U25.2, U28.13
unnamed: U27.1 (E), U28.11
VCC: C2.1, C3.1, C4.1, C7.1, C8.1, C9.1, C10.1, C11.1, C12.1, C13.1, C14.1, C15.1, C16.1, C18.1, C19.1, C20.1, C23.1, C24.1, C25.1, C26.1, C27.1, C28.1, C29.1, C30.1, C36.1, C37.1, C38.1, C39.1, C40.1, C41.1, C45.1, C46.1, C47.1, C48.1, C49.1, C50.1, C51.1, C52.1, C53.1, C54.1, C58.1, C59.1, C60.1, C62.1, C63.1, D6.2 (K), P3.1, P3.14, P5.1, P5.14, R1.2, R3.2, R4.1, R5.1, R7.2, R9.2, R11.1, R12.2, R14.2, R39.1, R41.1, RR2.1 (COM), RR3.1 (COM), RR4.1 (COM), RR5.1 (COM), RR6.1 (COM), RR7.1 (COM), RR8.1 (COM), RR9.1 (COM), U1.11 (VCC), U2.20 (VCC), U3.20 (VCC), U4.16 (VCC), U5.16 (VCC), U6.16 (VCC), U7.14 (VCC), U8.16 (VCC), U9.10 (Ds), U9.16 (VCC), U10.10 (Ds)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

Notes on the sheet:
2 MHz TTL OSCILLATOR
SPARES
Card Ejector Mounting Holes
Z80 ACTIVE
EXTERNAL CPU CLOCK (NDEF3)
Data Output Buffer Disable
A16
Active LOW when addressing Onboard ROM
ROM WAIT
A17
A18
A19
ROM Select LED

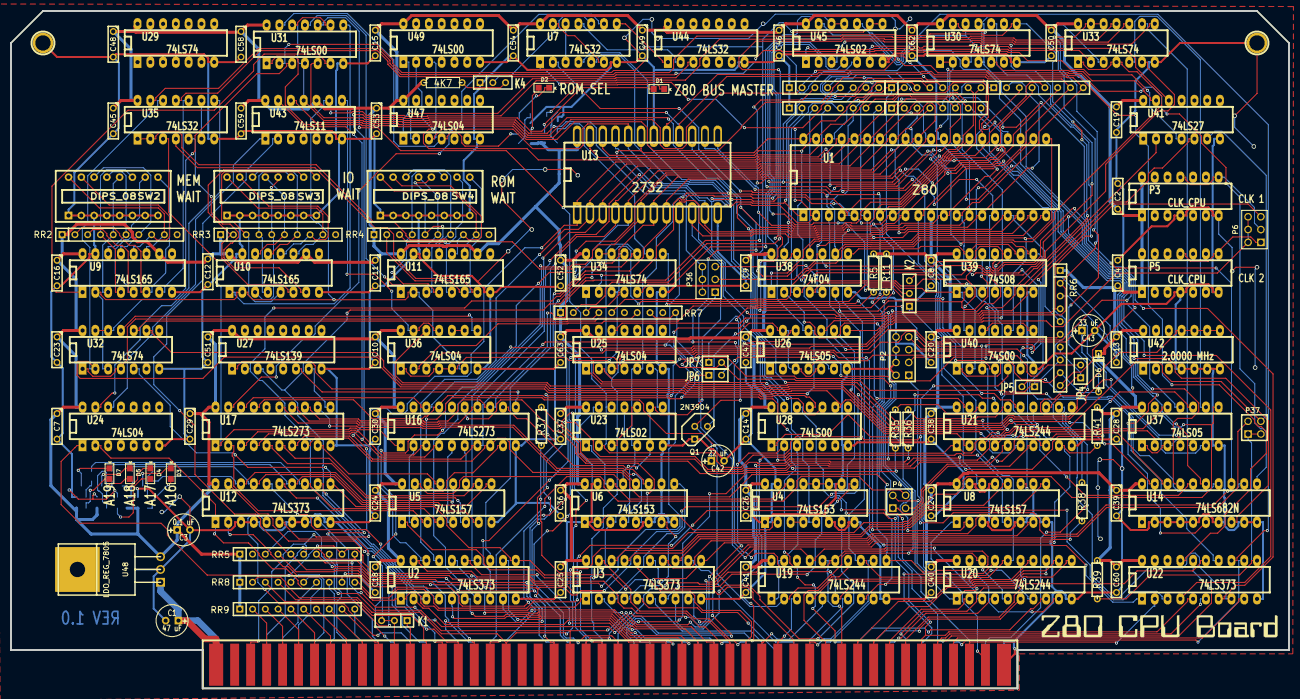
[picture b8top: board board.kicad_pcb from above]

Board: 2 copper layers, 254.0 x 134.6 mm, 163 parts (0 on the bottom side), 297 nets.

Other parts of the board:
Z80cpuV3: ***Z80cpuV3

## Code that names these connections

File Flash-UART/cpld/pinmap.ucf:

#PIN MAP OF U20 RS232 Serial Flash Board Verison 1


#------ OUTPUTS ------------------------------------------------------

NET "BUSOUTEN"    LOC =  "P21"; 	# Data Bus OUTPUT enable U3dout1
NET "BUSINEN"    	LOC =  "P22"; 	# Data Bus INPUT enable U3din1

NET "IOREQtoUx17"    LOC =  "P39"; 	#active high IOREQbb signal going to Ux17 pin 13 for UART CS
NET "RESET"    		LOC =  "P115"; 	# Reset to UART active high
NET "RD"    			LOC =  "P113"; 	# Read strobe to UART active low
NET "WR"    			LOC =  "P116"; 	# Write strobe to UART active low

NET "Diode2"    		LOC =  "P7"; 	# LED D2
NET "Diode3"    		LOC =  "P6"; 	# LED D3
NET "DONELED"    	LOC =  "P30"; 	# DONE LED
NET "BSLED"    	LOC =  "P31"; 	# Board Select LED

NET "RESTTOS100"    		LOC =  "P3"; 	# reset to system S100 bus pin 75
#NET "WAITTOS100"    		LOC =  "P2"; 	# wait to processor S100 bus pin 72 (RDY)

NET "FLASH0"    	LOC =  "P71"; 	# LED to indicate Flash 0 selected
NET "FLASH1"    	LOC =  "P74"; 	# LED to indicate Flash 1 selected
NET "FLASH2"    	LOC =  "P75"; 	# LED to indicate Flash 2 selected
NET "FLASH3"    	LOC =  "P76"; 	# LED to indicate Flash 3 selected
NET "FLASHSEL0"    	LOC =  "P66"; 	# CS line to Flash 0
NET "FLASHSEL1"    	LOC =  "P64"; 	# CS line to Flash 1
NET "FLASHSEL2"    	LOC =  "P61"; 	# CS line to Flash 2
NET "FLASHSEL3"    	LOC =  "P60"; 	# CS line to Flash 3

NET "TMA0"    		LOC =  "P117"; 	# to U11 TMA0 line 
NET "TMA1"    		LOC =  "P118"; 	# to U11 TMA1 line 
NET "TMA2"    		LOC =  "P119"; 	# to U11 TMA2 line 
NET "TMA3"    		LOC =  "P120"; 	# to U11 TMA3 line 

NET "Pin112"    		LOC =  "P112"; 	#
NET "Pin110"    		LOC =  "P110"; 	#

NET "FLASHCLK"    	LOC =  "P135"; 	#Flash CLK line (output to FLASH)
NET "FLASHDin"    	LOC =  "P136"; 	#Flash Din line (output to FLASH) Data from System to FLASH
NET "FLASHCSsys"    	LOC =  "P137"; 	#Flash CS line (output to FLASH)

NET "CPLD134"    		LOC =  "P134"; 	#to enable buffer U19 (connected to Data Bus)
NET "CPLD45"    		LOC =  "P45"; 		#to buffer U19 i.e. D0 (connected to Data Bus)

#------ INPUTS -------------------------------------------------------


NET "SOUTb"    	LOC =  "P34";   #active high - I/O WR (s100 Pin 45)
NET "SINPb"    	LOC =  "P35";   #active high - I/O RD (s100 Pin 46)
NET "pDBINb"    	LOC =  "P51";   #active high - when processor Reads from I/O or MEM (s100 Pin 78)
NET "pWRb"    		LOC =  "P50";   #active low - when processor Writes to I/O or MEM (s100 Pin 77)
NET "sMEMRb"    	LOC =  "P38";   #active high - MEM RD (s100 Pin 47)
NET "MWRTb"    	LOC =  "P40";   #active high - MEM WR (s100 Pin 68)

NET "SLAVECLR"    LOC =  "P33";   #active low - input reset from another board (s100 Pin 54)
NET "PHIb"    		LOC =  "P54";   #primary processor clock line (s100 Pin 24)
NET "CLOCKb"    	LOC =  "P53";   #clock line from another board (s100 Pin 49)



#-- INPUTs into this board but not used in the interest of S100 compatability --
#NET "M1"    		LOC =  "P20";   #NOT USED - M1 shows processor instruction fetch cycle (s100 Pin 44)
#NET "IOREQbb"    	LOC =  "P39";   #NOT USED - IOREQUEST (s100 Pin 69)
#NET "NDEF2b"    	LOC =  "P41";   # NOT USED -active low - MREQ Memory Reguest Signal (s100 Pin 65)
#NET "sWOb"    		LOC =  "P52";   #NOT USED - active low when processor is in Write status (s100 Pin 97)
#-------------------------------------------------------------------------------

NET "A0"    	LOC =  "P100";   #Address Line 
NET "A1"    	LOC =  "P101";   #Address Line 
NET "A2"    	LOC =  "P102";   #Address Line 
NET "A3"    	LOC =  "P103";   #Address Line 
NET "A4"    	LOC =  "P104";   #Address Line 
NET "A5"    	LOC =  "P105";   #Address Line 
NET "A6"    	LOC =  "P106";   #Address Line 
NET "A7"    	LOC =  "P107";   #Address Line 
#NET "A8"    	LOC =  "P79";   #Address Line 
#NET "A9"    	LOC =  "P80";   #Address Line 
#NET "A10"    	LOC =  "P81";   #Address Line 
#NET "A11"    	LOC =  "P82";   #Address Line 
#NET "A12"    	LOC =  "P83";   #Address Line 
#NET "A13"    	LOC =  "P85";   #Address Line 
#NET "A14"    	LOC =  "P86";   #Address Line 
#NET "A15"    	LOC =  "P87";   #Address Line 
#NET "A16"    	LOC =  "P88";   #Address Line 
#NET "A17"    	LOC =  "P91";   #Address Line 
#NET "A18"    	LOC =  "P92";   #Address Line 
#NET "A19"    	LOC =  "P93";   #Address Line 
#NET "A20"    	LOC =  "P94";   #Address Line 
#NET "A21"    	LOC =  "P95";   #Address Line 
#NET "A22"    	LOC =  "P96";   #Address Line 
#NET "A23"    	LOC =  "P97";   #Address Line 

NET "D0"    	LOC =  "P9";   #Data Line 
NET "D1"    	LOC =  "P10";   #Data Line 
NET "D2"    	LOC =  "P11";   #Data Line 
NET "D3"    	LOC =  "P12";   #Data Line 
#NET "D4"    	LOC =  "P13";   #Data Line 
#NET "D5"    	LOC =  "P14";   #Data Line 
#NET "D6"    	LOC =  "P15";   #Data Line 
#NET "D7"    	LOC =  "P16";   #Data Line 

NET "D0b"    	LOC =  "P17";   #Data Line 
NET "D1b"    	LOC =  "P19";   #Data Line 


NET "CSUART"    	LOC =  "P25";   #CS UART line (input to CPLD to be able to select Data buffers WR/RD)
NET "MASTERRESET"    	LOC =  "P24";   #Board Maset Reset button

NET "PIC18F0"    	LOC =  "P68";   #from 18F1330 for Flash Select 
NET "PIC18F1"    	LOC =  "P69";   #from 18F1330 for Flash Select 
NET "PIC18F2"    	LOC =  "P70";   #from 18F1330 for Flash Select  

NET "FLASHCS"    	LOC =  "P57";   #Master Flash CS from either RUN or PROG

NET "FLASHDout"    LOC =  "P138"; 	#Flash Dout line (input, from FLASH) Data from FLASH to System.

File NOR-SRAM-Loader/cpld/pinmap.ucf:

#PIN MAP OF U11 on 8Mb Serial NOR to 1MB SRAM board


#------ OUTPUTS ------------------------------------------------------

NET "RESET"    LOC =  "P1";
#NET "CPLD53WAIT"    LOC =  "P53";   #to S100 bus pin72 - WAIT* to MASTER board
NET "BSELLED"    LOC =  "P8";   #Board Select LED output
NET "BROMLED"    LOC =  "P54";   #Board ROM LED output
NET "BMEMLED"    LOC =  "P55";   #Board MEM - SRAM selected LED
NET "DONELED"    LOC =  "P6";   #Board load to Memory DONE LED

NET "CPLDP12ROM1OE"    LOC =  "P12";   #to UVEPROM OE active low
NET "CPLDP92ROM1CS"    LOC =  "P92";   #to UVEPROM CS active low

NET "DBUSOUTEN"    	LOC =  "P13";   #active low - for slave Data OUTPUT
NET "DBUSINEN"    	LOC =  "P18";   #active low - for slave Data INPUT


NET "CPLD_59"    	LOC =  "P59";   #active low output to pin19 of U26, U25, U24 - RAM/ROM2 Buffers
NET "U23DIR"    	LOC =  "P56";   #U23 Direction - Data Bus Buffer to RAM/ROM2
NET "U23CE"    	LOC =  "P58";   #U23 Chip Enable  - active low -

NET "ROM2_0_CS"   LOC =  "P9";   # ROM2 low bank CS
NET "ROM2_1_CS"   LOC =  "P11";   #ROM2 high bank CS
NET "ROM2_OE"    	LOC =  "P10";   #ROM2 OE
NET "ROM2_WE"    	LOC =  "P78";   #ROM2 WE

NET "PINCPLD79"    	LOC =  "P79";   #out pin header to pin 79 of cpld
NET "PINCPLD90"    	LOC =  "P90";   #out pin header to pin 90 of cpld
NET "PINCPLD89"    	LOC =  "P89";   #out pin header to pin 89 of cpld

NET "NOR_CLK"    		LOC =  "P93";   	#
NET "NOR_DIN"    		LOC =  "P95";   	#(Data from System to 25P80) at 0x81
NET "NOR_CS"    		LOC =  "P96";   	#
NET "NOR_DOUT"    	LOC =  "P97";   	#Dout (Data from 25P80 into System at 0x83


#------ INPUTS -------------------------------------------------------


NET "BOARDSELECT"    LOC =  "P41";   #board select from 74LS682

NET "sM1"    			LOC =  "P16";   #sM1 active high when processor is in instruction fetch
NET "sOUT"    			LOC =  "P65";   #active high - I/O WR
NET "sINP"    			LOC =  "P67";   #active high - I/O RD
NET "sMEMR"    		LOC =  "P71";   #active high - MEM RD
NET "IOREQb"    		LOC =  "P72";   #active low - IORQ
NET "MWRT"    			LOC =  "P68";   #active high - MEM WR
NET "NDEF2"    		LOC =  "P76";   #active low - MREQ
NET "SLAVECLRvv"    	LOC =  "P85";   #reset input from another board - from the MASTER

NET "pWR"    			LOC =  "P70";   #active low - when processor Writes to I/O or MEM
NET "pDBIN"    		LOC =  "P66";   #active high - when processor Reads from I/O or MEM
NET "sWO"    			LOC =  "P81";   #
NET "CLOCK"    		LOC =  "P23";   #clock line from another board - s100 pin49
NET "PHI"    			LOC =  "P27";   #Primary Processor Clock line - S100 pin24

NET "A0"    		LOC =  "P14";   #
NET "A1"    		LOC =  "P15";   #
NET "A2"    		LOC =  "P25";   #
NET "A3"    		LOC =  "P17";   #
NET "A4"    		LOC =  "P28";   #
NET "A5"    		LOC =  "P33";   #
NET "A6"    		LOC =  "P74";   #
NET "A7"    		LOC =  "P82";   #
NET "A8"    		LOC =  "P61";   #
NET "A9"    		LOC =  "P50";   #
NET "A10"    		LOC =  "P42";   #
NET "A11"    		LOC =  "P60";   #
NET "A12"    		LOC =  "P64";   #
NET "A13"    		LOC =  "P77";   #
NET "A14"    		LOC =  "P63";   #
NET "A15"    		LOC =  "P86";   #

NET "A20"    		LOC =  "P32";   #
NET "A21"    		LOC =  "P49";   #
NET "A22"    		LOC =  "P35";   #
NET "A23"    		LOC =  "P37";   #

NET "D0"    		LOC =  "P36";   #
NET "D1"    		LOC =  "P29";   #
NET "D2"    		LOC =  "P39";   #
NET "D3"    		LOC =  "P30";   #
NET "D4"    		LOC =  "P40";   #
NET "D5"    		LOC =  "P87";   #
NET "D6"    		LOC =  "P94";   #
NET "D7"    		LOC =  "P91";   #

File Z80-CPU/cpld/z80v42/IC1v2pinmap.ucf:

#PIN MAP OF IC1 on Z80 Board V4
#Date: 30-06-2015
# Target XC9572 PC84

#24+22+16=62

#29+33

#------ OUTPUTS ------------------------------------------------------;24


NET "CPLD_CLKout1"    	LOC =  "P10";   #Clock output
NET "CPLD_CLKout2"    	LOC =  "P12";   #Clock output

NET "RomEn"    	LOC =  "P37";   #Rom enable line from U36 pin5

NET "SINPb"    	LOC =  "P13";   #active high - I/O RD (s100 Pin 46)
NET "sMEMRb"    	LOC =  "P18";   #active high - MEM RD (s100 Pin 47)
NET "sWOb"    		LOC =  "P20";   #active low - Write Output (s100 Pin 97)
NET "SOUTb"    LOC =  "P48";   #active high - I/O WR (s100 Pin 45)
NET "sINTAb"    	LOC =  "P14";   # interrupt ack (s100 Pin 96)

NET "Resout"    LOC =  "P23";   #CPLD reset output- made from button and/or slave clr . i.e via button on board

#NET "U17OE"    LOC =  "P32";   #U17 OE
#NET "U17A"    	LOC =  "P31";   #Data input to bufffer (data 0).

NET "M1pos"    	LOC =  "P19"; 	# negated M1* from CPU
NET "pSYNCb"   	LOC =  "P46";   # (s100 Pin 76)
NET "WAITen"    	LOC =  "P44";   #(s100 Pin 25)
NET "pWRb"    		LOC =  "P51";   #active low - when processor Writes to I/O or MEM (s100 Pin 77)
NET "WRpos"    	LOC =  "P52"; 	# negated WR* from CPU
NET "MREQpos"    LOC =  "P47"; 	# negated MREQ* from CPU
NET "IORQpos"    LOC =  "P54"; 	# negated IORQ* from CPU
NET "RDpos"    	LOC =  "P55"; 	# negated RD* from CPU
NET "PartialLatch"    		LOC =  "P66"; 	# partial latch output 
NET "MWRTb"    	LOC =  "P69";   #active high - MEM WR (s100 Pin 68)

NET "LED_D4"    	LOC =  "P39";   # LED D4
NET "LED_D5"    	LOC =  "P40";   # LED D5
NET "LED_D6"    	LOC =  "P41";   # LED D6
NET "LED_D7"    	LOC =  "P81";   # LED D7
#NET "LED_D9"    	LOC =  "P62";   # LED D9
#NET "LED_D10"    	LOC =  "P50";   # LED D10

NET "P75"    	LOC =  "P75";   #pin 75 i/o pin on board header
NET "P79"    	LOC =  "P79";   #pin 79 i/o pin on board header
NET "P77"    	LOC =  "P77";   #pin 77 i/o pin on board header
NET "P3"    	LOC =  "P3";    #pin 3 i/o pin on board header



#------ INPUTS -------------------------------------------------------;22


NET "RomAddr"    	LOC =  "P45";   #Rom Address range being addresses by CPU - Active HIGH

NET "CLKin"    LOC =  "P9"; 	# MASTER CPU clock input

NET "WRneg"    	LOC =  "P1"; 	# WR* from CPU
NET "MREQneg"    LOC =  "P6"; 	# MREQ* from CPU
NET "REFSHneg"   LOC =  "P11"; 	# REFSH* from CPU
NET "WAITpos"    	LOC =  "P25";   # WAIT+ signal from wait generators
#NET "slaveCLRneg"    LOC =  "P15";   #Slave CLEAR (pin54 S100)
NET "RESb"    LOC =  "P17";   # Reset into CPU from onboard logic
NET "Resbut"  LOC =  "P76";   #Slave clear button on board
NET "IORQneg"    LOC =  "P63"; 	# IORQ* from CPU
#NET "PortD1b7"    LOC =  "P67"; 	# from PortD1 bit 7 on board.
NET "RDneg"    	LOC =  "P72"; 	# RD* from CPU
NET "M1neg"    	LOC =  "P84"; 	# M1* from CPU
#NET "PortD0b7"    LOC =  "P65"; 	# from PortD0 bit 7 on board.

NET "A0"    	LOC =  "P80";   	#Address Line 
NET "A1"    	LOC =  "P83";   	#Address Line 
NET "A2"    	LOC =  "P82";   	#Address Line 
NET "A3"    	LOC =  "P7";   	#Address Line 
NET "A4"    	LOC =  "P2";   	#Address Line 
NET "A5"    	LOC =  "P43";   	#Address Line 
NET "A6"    	LOC =  "P36";   	#Address Line 
NET "A7"    	LOC =  "P71";   	#Address Line 

NET "D0in"    	LOC =  "P33";   #Data Line 


NET "PortD0b7LED"    	LOC =  "P65";   #Port D0 bit 7 (to LED D6)
NET "PortD1b7LED"    	LOC =  "P67";   #Port D1 bit 7 (to LED D7)

#------ I/O -------------------------------------------------------;16

#NET "P8_1"    	LOC =  "P34"; 	# 
#NET "P8_2"    	LOC =  "P35"; 	# 
#NET "P8_3"    	LOC =  "P21"; 	# 
#NET "P8_4"    	LOC =  "P26"; 	# 
#NET "P8_5"    	LOC =  "P68"; 	# 
#NET "P8_6"    	LOC =  "P70"; 	# 
#NET "P8_7"    	LOC =  "P57"; 	# 
#NET "P8_8"    	LOC =  "P53"; 	# 
#NET "P8_9"    	LOC =  "P58"; 	# 
#NET "P8_10"    LOC =  "P61"; 	# 
#NET "P8_11"    LOC =  "P74"; 	# 

#NET "P11_2"    LOC =  "P75"; 	# 
#NET "P11_3"    LOC =  "P79"; 	# 
#NET "P11_4"    LOC =  "P4"; 	#
#NET "P11_5"    LOC =  "P77"; 	#  
#NET "P11_6"    LOC =  "P3"; 	# 
